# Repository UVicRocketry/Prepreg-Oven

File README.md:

# ThePrepregOvenProject
Circuit diagram, Arduino code, etc. related to the Prepreg Oven Project: Uvic Rocketry's custom composite curing oven! 

The PPO is capable of reading custom temperature profiles from an SD card. Users can load up to 999 profiles with up to 20 target tempertures. Temperature values are linearly interpolated automatically.

## Interface
The oven has 2 buttons for controlling various functions:

**SELECT** Used for scrolling through temperature profiles.

**START/STOP** Confirms temperature profile and starts the oven. Long press to force shut down oven mid cycle. Long press again to reboot the oven.

## Starting the Oven
Upon first power, or after rebooting, the oven displays the profile selection screen. 

Pressing the SELECT button scrolls through the temperature profiles stored on the SD card. The numerical name of the file is displayed, and a short description of the profile appears below.

Once the desired profile is displayed, press START to begin the profile.

## Creating Temperature Profiles
Temperature profiles can be loaded on the SD card for custom cycles.

The format for a profile is a single line in the file as follows:
- Numerical filenames starting at 0. No file extension.
- Exactly 14 alphnumeric characters describing the profile. Pad with spaces if needed. Terminate with a `,`.
- Up to 40 `,` seperated non negative integer values alternating between temperature in C and time between temperatures in seconds. The maximum value of a time number is `65535` (~18h in seconds), and maximum temperature value is `200`.

For example, a profile called `0` containing the single line of text: `Sample        ,20,1800,50,5400,50,1800,80,7200,80,1800,120,1800,120,3600,20` produces the cycle in the image below.

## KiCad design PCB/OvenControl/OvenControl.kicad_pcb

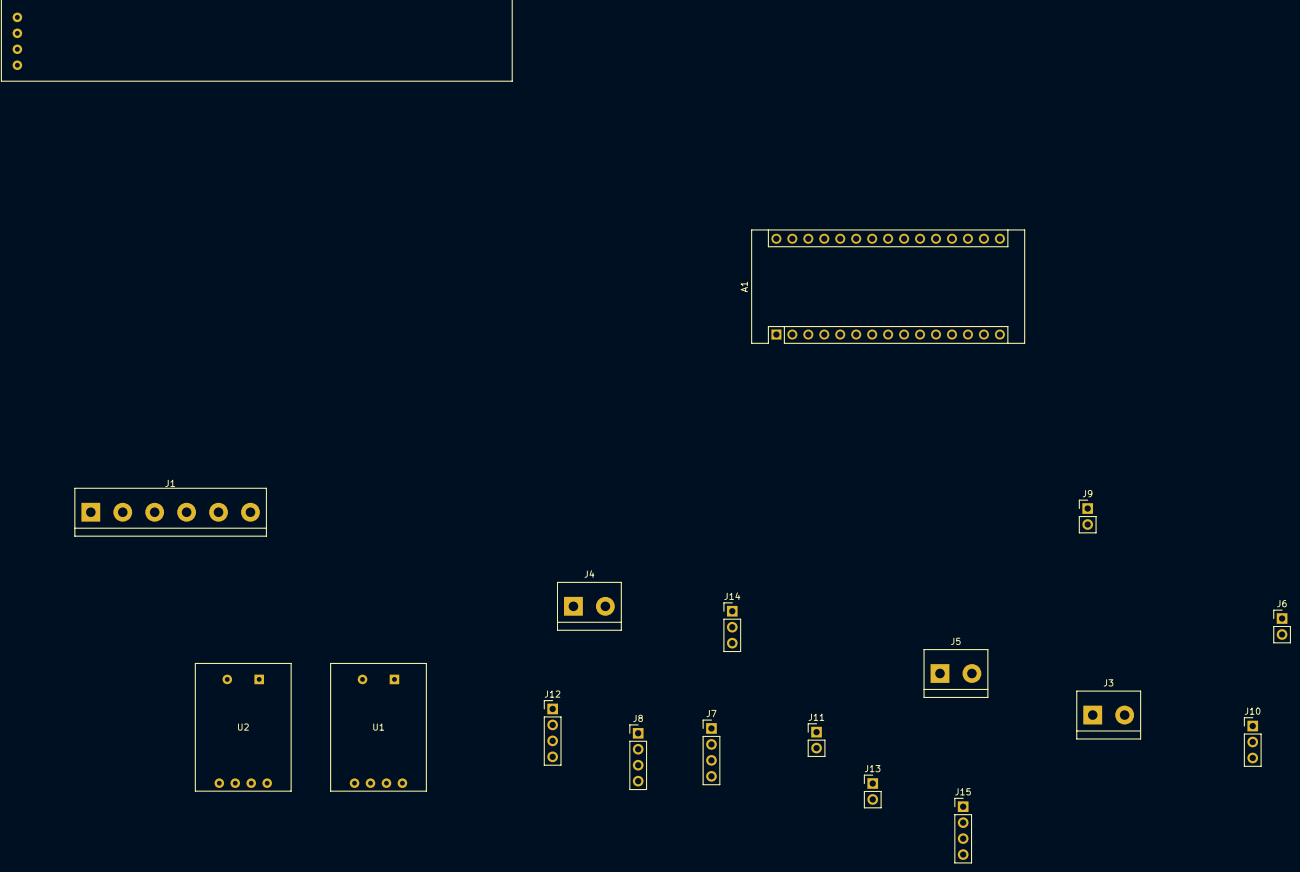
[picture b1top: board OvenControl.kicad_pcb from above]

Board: 2 copper layers, 18 parts (0 on the bottom side), 19 nets, no tracks yet.

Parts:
A1: Arduino_Nano_v3.x; Arduino_Nano
J1: Screw_Terminal_01x06; TerminalBlock_bornier-6_P5.08mm
J3, J4, J5: Screw_Terminal_01x02; TerminalBlock_bornier-2_P5.08mm
J6, J9: Conn_01x02_Female; PinHeader_1x02_P2.54mm_Vertical
J7, J8: Conn_01x04_Female; PinHeader_1x04_P2.54mm_Vertical
J10: Conn_01x03_Female; PinHeader_1x03_P2.54mm_Vertical
J11, J13: Conn_01x02_Male; PinHeader_1x02_P2.54mm_Vertical
J12, J15: Conn_01x04_Male; PinHeader_1x04_P2.54mm_Vertical
J14: Conn_01x03_Male; PinHeader_1x03_P2.54mm_Vertical
U1, U2: ADAFRUIT_AD8495; thermoucouple_AD8495
U3: LCD_SCREEN

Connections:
/+5V: A1.27, J8.3, U1.4, U2.4
/+12V: A1.30, J6.1
/AC_Dimmer_PWM: A1.5, J7.2
/AC_Dimmer_Z-C: A1.10, J7.1
/LCD_SDA: A1.23, J8.1
/LCD_SDL: A1.24, J8.2
/Rotary_Encoder1_Input: A1.7, J10.1
/Rotary_Encoder1_PWM: A1.6, J10.2
/Thermocouple1: A1.22, U1.2
/Thermocouple1+: J3.1, U1.5
/Thermocouple1-: J3.2, U1.6
/Thermocouple2: A1.21, U2.2
/Thermocouple2+: J4.1, U2.5
/Thermocouple2-: J4.2, U2.6
GND: A1.4, J5.1, J5.2, J6.2, J7.3, J8.4, J9.2, J10.3, J13.2, J14.3, U1.1, U1.3, U2.1, U2.3
unnamed: J15.1, U3.4
unnamed: J15.2, U3.3
unnamed: J15.3, U3.2
unnamed: J15.4, U3.1

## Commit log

2022-02-20 Moves from GrabCAD
2022-02-23 Adds functions. Completes updateDisplay()
2022-02-23 Finishes interpolateTemp and measureTemp
2022-03-12 Add some SD support, and memes
2022-03-12 Add reset functionality
2022-03-13 Add basic csv reading
2022-03-13 Add full SD support. Remove some bugs
2022-03-13 Fix profile array overwriting bug
2022-03-16 More descriptive LCD UI
2022-03-16 Add PID loop
2022-03-18 Change to float for interpolation.
2022-03-19 Add GrabCAD PCB files
2022-04-14 Add wiring diagram
